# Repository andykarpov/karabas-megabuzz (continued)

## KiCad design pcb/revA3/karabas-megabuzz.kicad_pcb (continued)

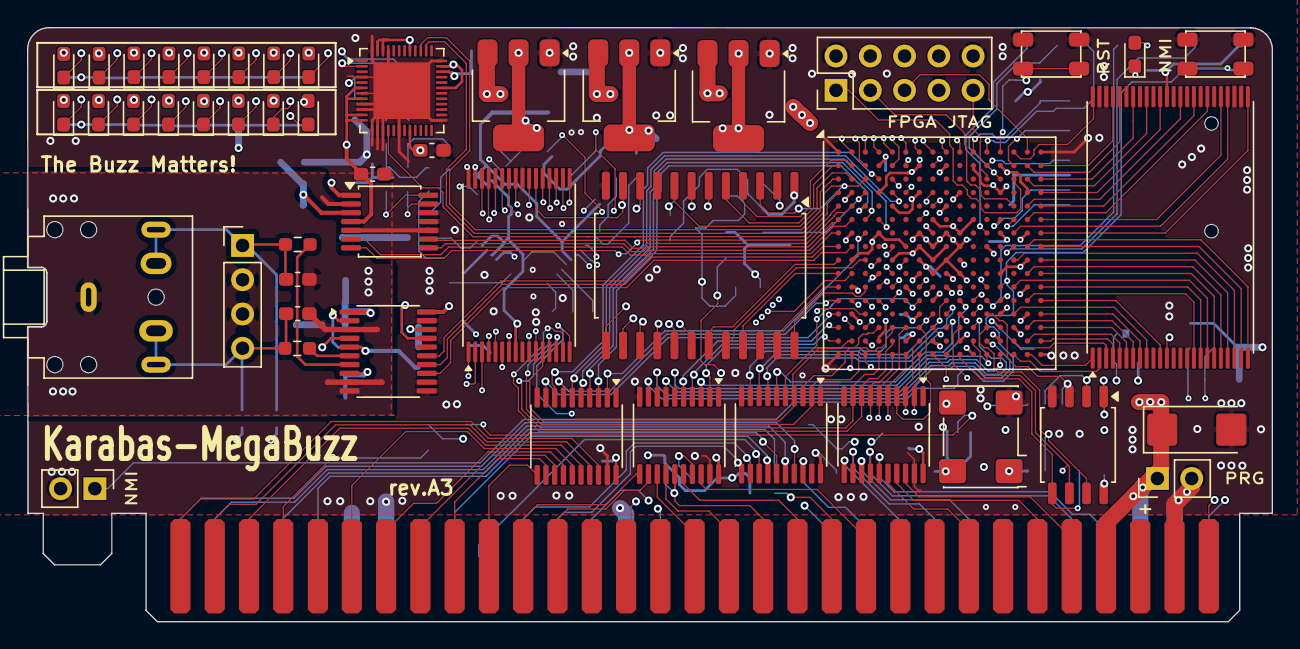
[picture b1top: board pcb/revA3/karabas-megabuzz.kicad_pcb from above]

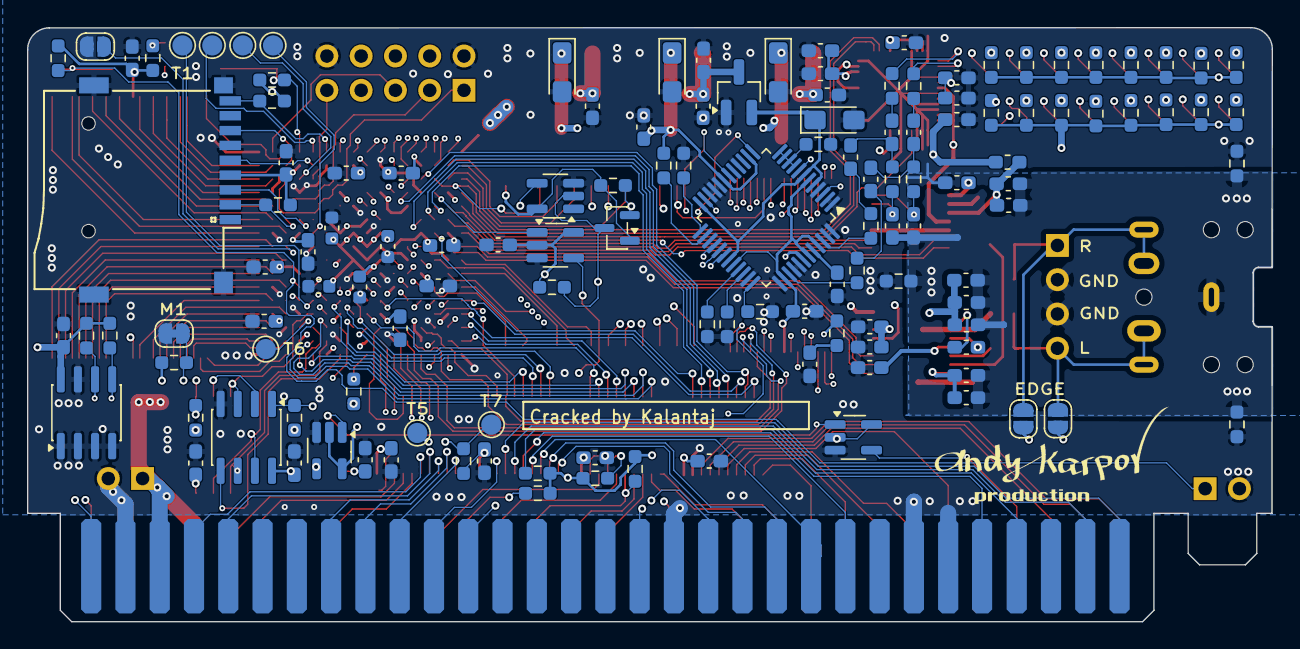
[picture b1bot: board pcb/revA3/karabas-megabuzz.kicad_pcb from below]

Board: 4 copper layers, 92.2 x 44.0 mm, 180 parts (132 on the bottom side), 245 nets.

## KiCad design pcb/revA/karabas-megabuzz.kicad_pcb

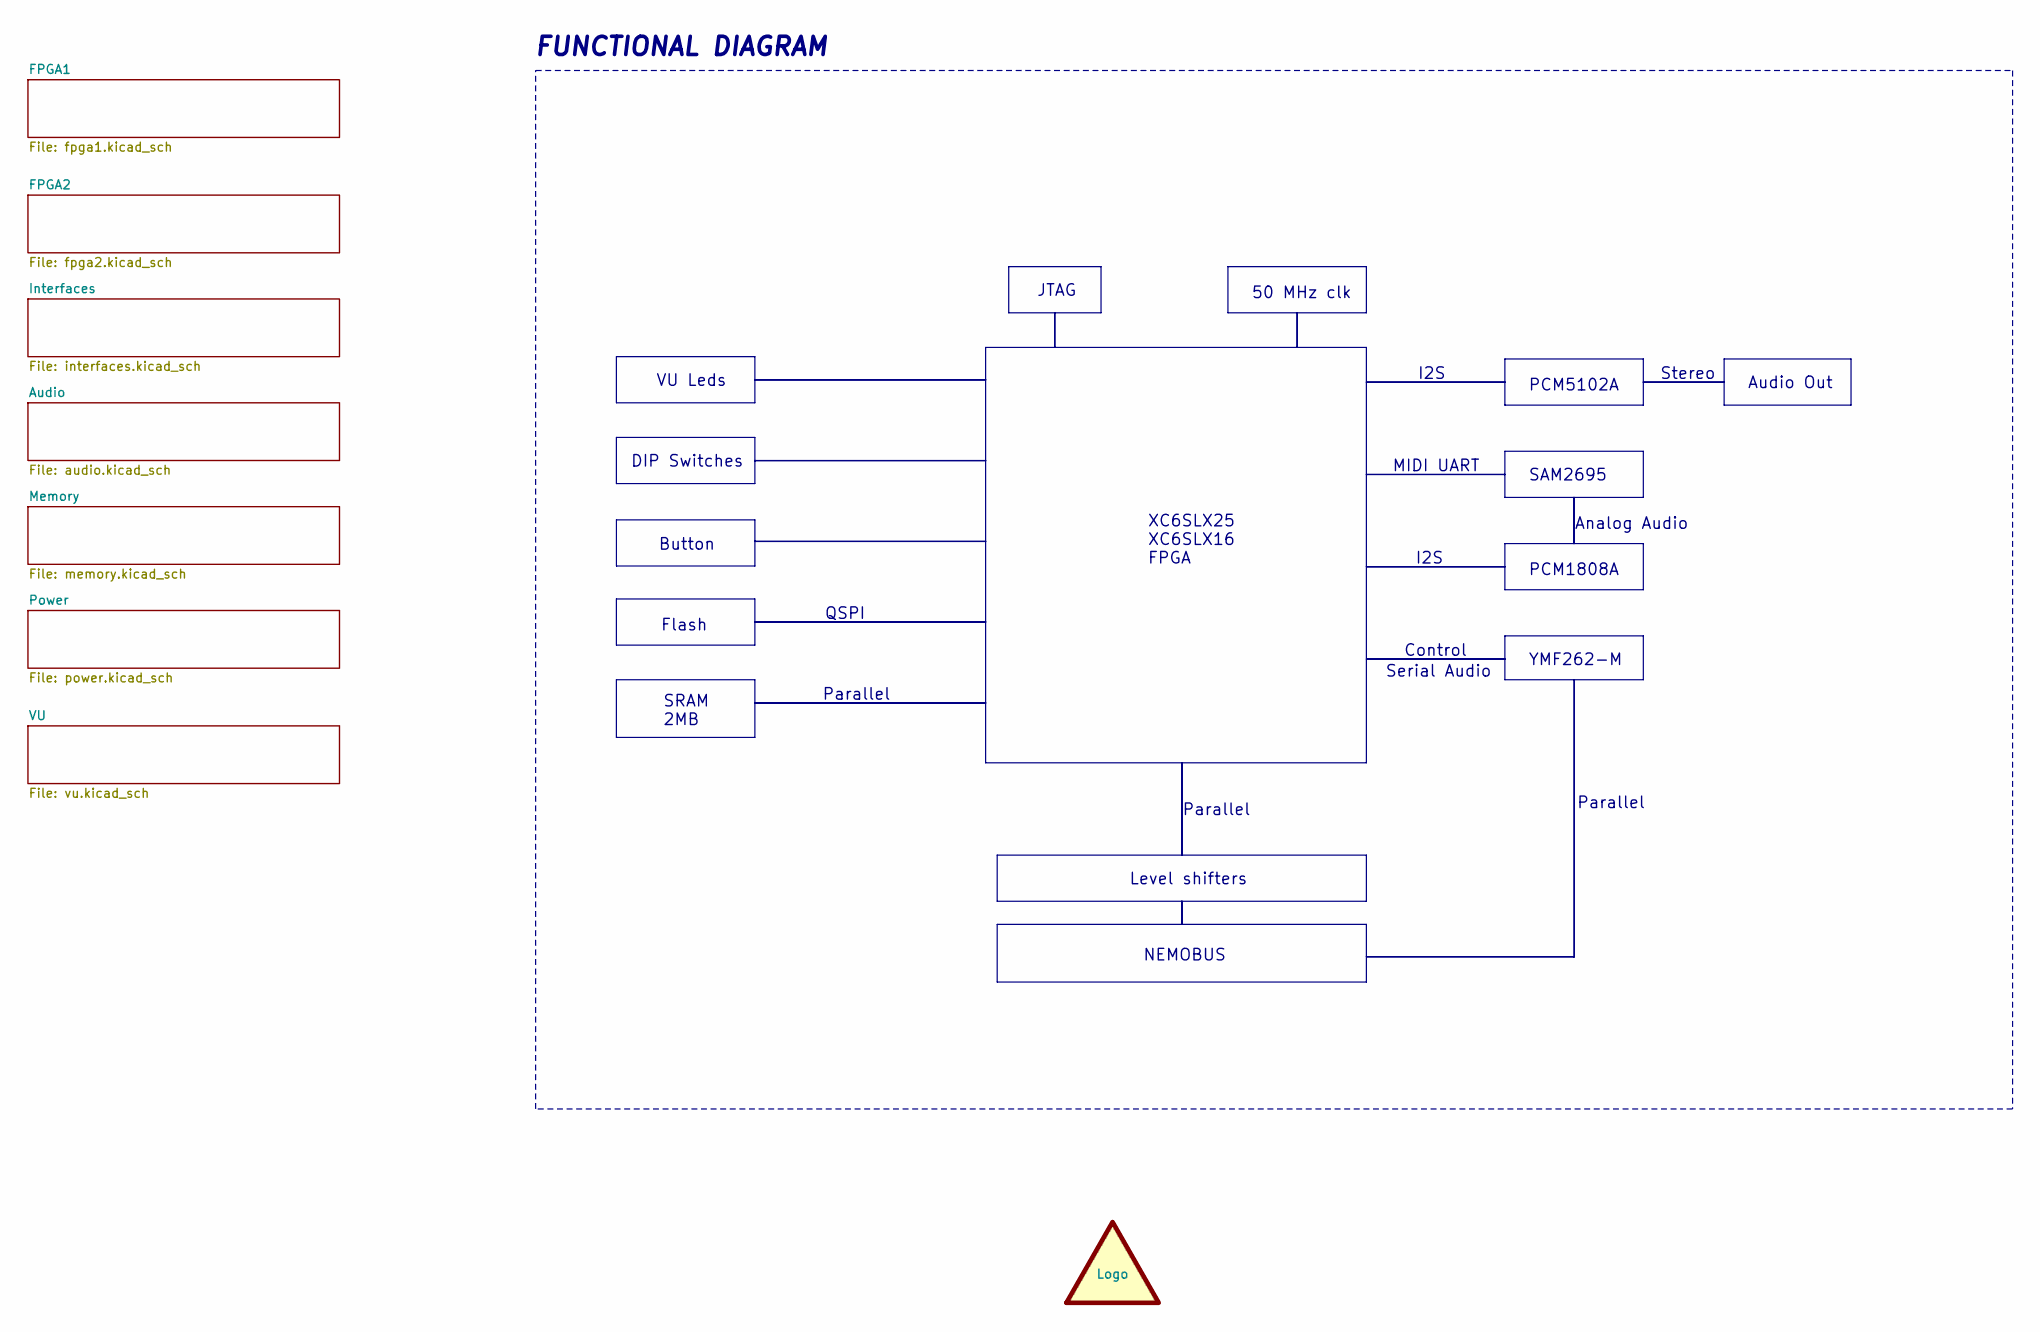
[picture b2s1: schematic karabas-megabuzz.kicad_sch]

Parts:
LOGO2: graphic; andy_karpov_logo4_silk

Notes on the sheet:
PCM5102A
VU Leds
XC6SLX25 XC6SLX16 FPGA
MIDI UART
Button
PCM1808A
Parallel
YMF262-M
NEMOBUS
DIP Switches
Audio Out
I2S
JTAG
Analog Audio
QSPI
50 MHz clk
Flash
SRAM 2MB
Level shifters
Control
Serial Audio
FUNCTIONAL DIAGRAM
SAM2695
Stereo

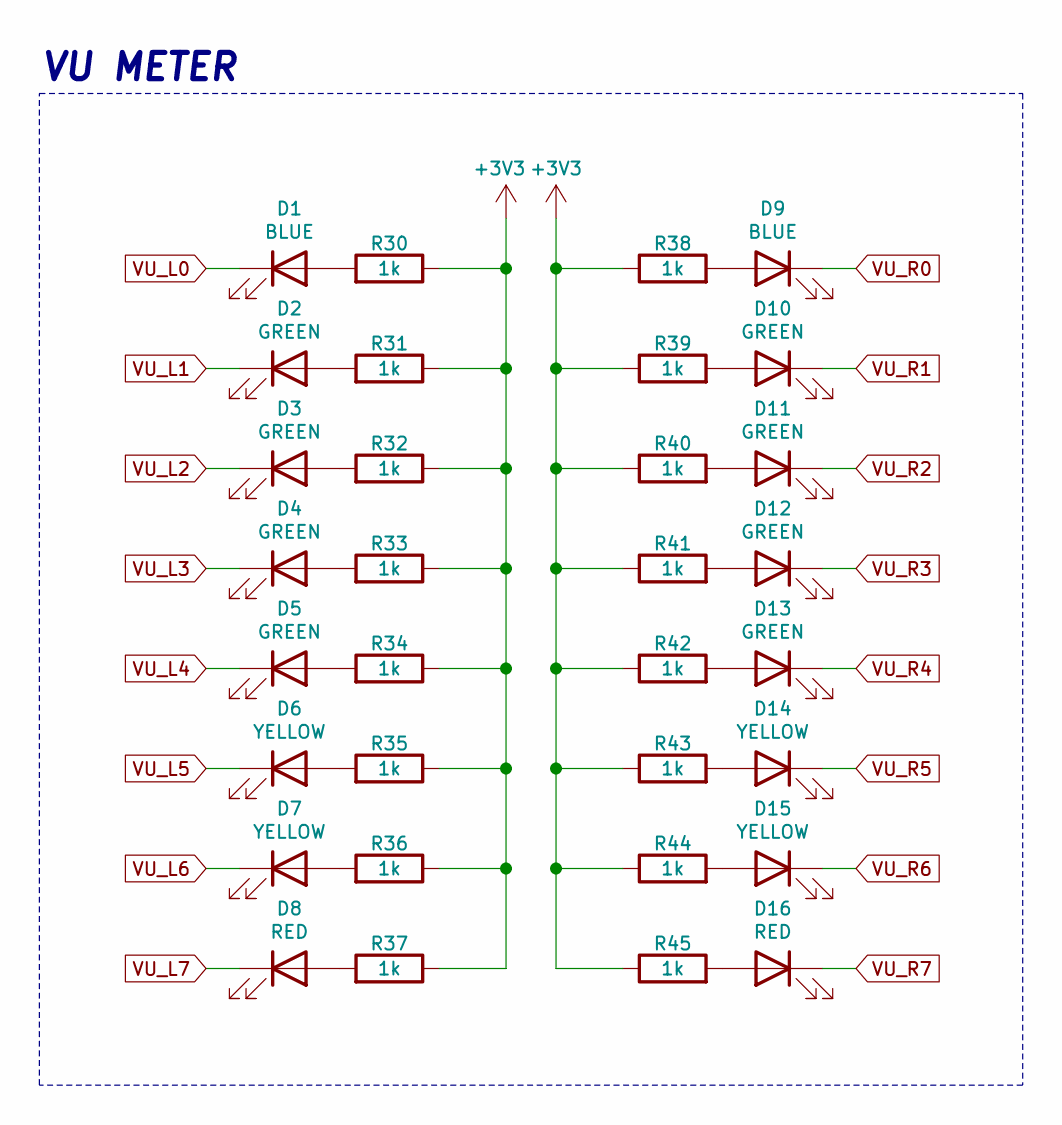
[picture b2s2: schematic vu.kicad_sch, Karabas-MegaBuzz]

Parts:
D1, D9: BLUE; LED_0603_1608Metric_Pad1.05x0.95mm_HandSolder
D2, D3, D4, D5, D10, D11, D12, D13: GREEN; LED_0603_1608Metric_Pad1.05x0.95mm_HandSolder
D6, D7, D14, D15: YELLOW; LED_0603_1608Metric_Pad1.05x0.95mm_HandSolder
D8, D16: RED; LED_0603_1608Metric_Pad1.05x0.95mm_HandSolder
R30, R31, R32, R33, R34, R35, R36, R37, R38, R39, R40, R41, R42, R43, R44, R45: 1k; R_0603_1608Metric_Pad0.98x0.95mm_HandSolder

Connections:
+3V3: R30.1, R31.1, R32.1, R33.1, R34.1, R35.1, R36.1, R37.1, R38.1, R39.1, R40.1, R41.1, R42.1, R43.1, R44.1, R45.1; also elsewhere on the board
unnamed: D1.2 (A), R30.2
unnamed: D2.2 (A), R31.2
unnamed: D3.2 (A), R32.2
unnamed: D4.2 (A), R33.2
unnamed: D5.2 (A), R34.2
unnamed: D6.2 (A), R35.2
unnamed: D7.2 (A), R36.2
unnamed: D8.2 (A), R37.2
unnamed: D9.2 (A), R38.2
unnamed: D10.2 (A), R39.2
unnamed: D11.2 (A), R40.2
unnamed: D12.2 (A), R41.2
unnamed: D13.2 (A), R42.2
unnamed: D14.2 (A), R43.2
unnamed: D15.2 (A), R44.2
unnamed: D16.2 (A), R45.2
VU_L0: D1.1 (K); also elsewhere on the board
VU_L1: D2.1 (K); also elsewhere on the board
VU_L2: D3.1 (K); also elsewhere on the board
VU_L3: D4.1 (K); also elsewhere on the board
VU_L4: D5.1 (K); also elsewhere on the board
VU_L5: D6.1 (K); also elsewhere on the board
VU_L6: D7.1 (K); also elsewhere on the board
VU_L7: D8.1 (K); also elsewhere on the board
VU_R0: D9.1 (K); also elsewhere on the board
VU_R1: D10.1 (K); also elsewhere on the board
VU_R2: D11.1 (K); also elsewhere on the board
VU_R3: D12.1 (K); also elsewhere on the board
VU_R4: D13.1 (K); also elsewhere on the board
VU_R5: D14.1 (K); also elsewhere on the board
VU_R6: D15.1 (K); also elsewhere on the board
VU_R7: D16.1 (K); also elsewhere on the board

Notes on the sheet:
VU METER

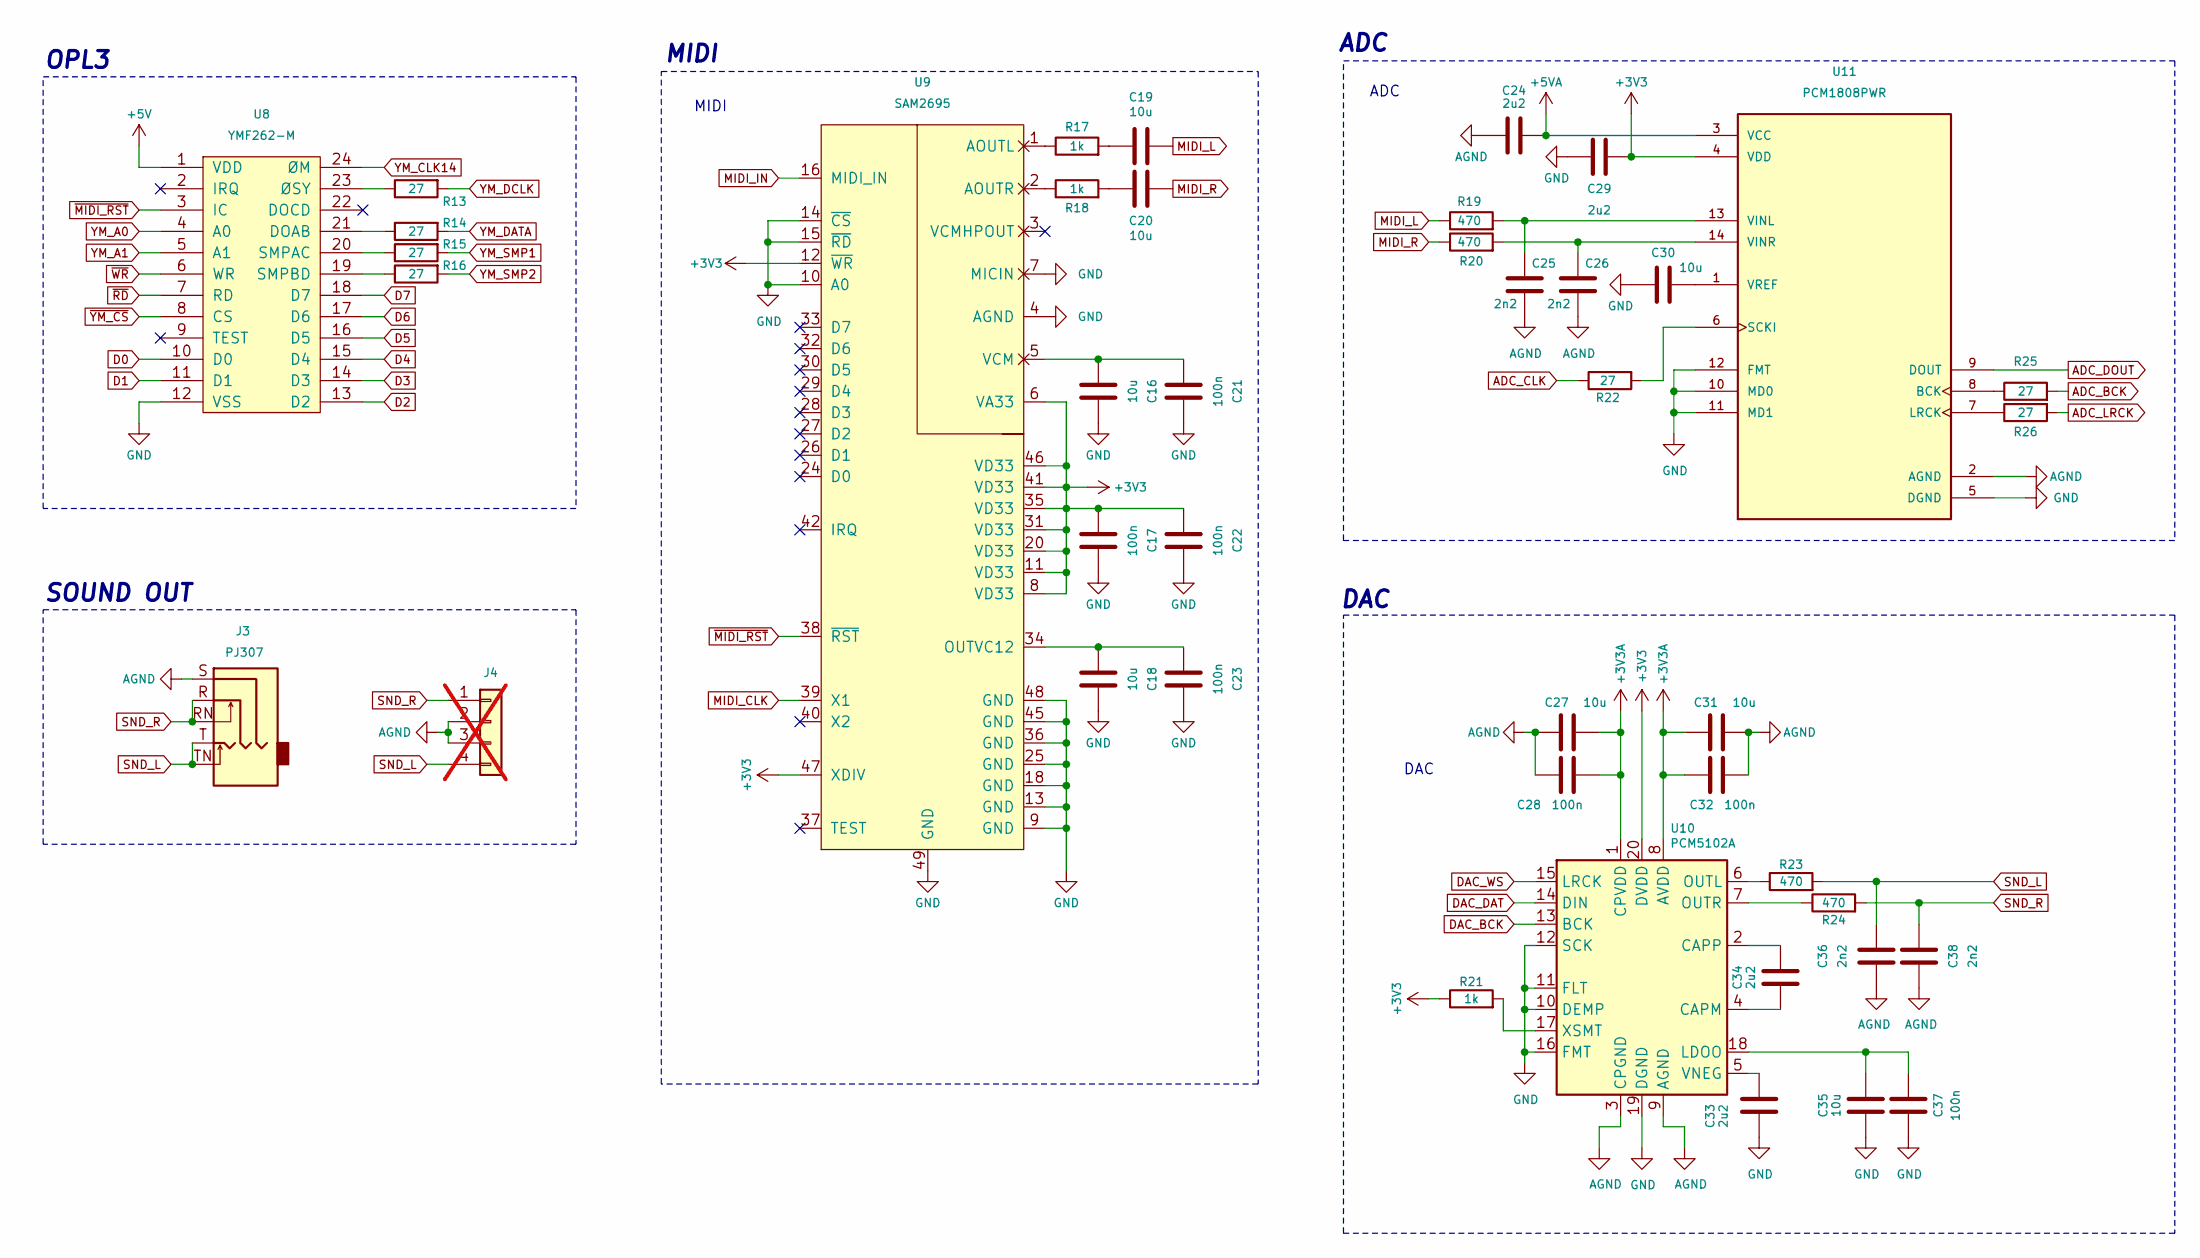
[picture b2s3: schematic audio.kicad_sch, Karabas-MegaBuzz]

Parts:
C16, C18, C19, C20, C27, C30, C31, C35: 10u; C_0603_1608Metric_Pad1.08x0.95mm_HandSolder
C17, C21, C22, C23, C28, C32, C37: 100n; C_0603_1608Metric_Pad1.08x0.95mm_HandSolder
C24, C29, C33, C34: 2u2; C_0603_1608Metric_Pad1.08x0.95mm_HandSolder
C25, C26, C36, C38: 2n2; C_0603_1608Metric_Pad1.08x0.95mm_HandSolder
J3: PJ307; Jack_3.5mm_CUI_SJ1-3525N_Horizontal
J4: Conn_01x04; PinHeader_1x04_P2.54mm_Vertical; not fitted
R13, R14, R15, R16, R22, R25, R26: 27; R_0603_1608Metric_Pad0.98x0.95mm_HandSolder
R17, R18, R21: 1k; R_0603_1608Metric_Pad0.98x0.95mm_HandSolder
R19, R20, R23, R24: 470; R_0603_1608Metric_Pad0.98x0.95mm_HandSolder
U8: YMF262-M; ymf-262-m
U9: SAM2695; QFN-48-1EP_6x6mm_P0.4mm_EP4.2x4.2mm
U10: PCM5102A; TSSOP-20_4.4x6.5mm_P0.65mm
U11: PCM1808PWR; TSSOP-14_4.4x5mm_P0.65mm; PARTREV B

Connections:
+3V3: C17.1, C22.1, C29.1, R21.1, U9.6 (VA33), U9.8 (VD33), U9.11 (VD33), U9.12 (~WR), U9.20 (VD33), U9.31 (VD33), U9.35 (VD33), U9.41 (VD33), U9.46 (VD33), U9.47 (XDIV), U10.20 (DVDD), U11.4 (VDD); also elsewhere on the board
+3V3A: C27.1, C28.1, C31.2, C32.2, U10.1 (CPVDD), U10.8 (AVDD); also elsewhere on the board
+5V: U8.1 (VDD); also elsewhere on the board
+5VA: C24.2, U11.3 (VCC); also elsewhere on the board
ADC_BCK: R25.2; also elsewhere on the board
ADC_CLK: R22.1; also elsewhere on the board
ADC_DOUT: U11.9 (DOUT); also elsewhere on the board
ADC_LRCK: R26.2; also elsewhere on the board
AGND: C24.1, C25.2, C26.2, C27.2, C28.2, C31.1, C32.1, C36.1, C38.1, J3.S, J4.2, J4.3, U10.3 (CPGND), U10.9 (AGND), U11.2 (AGND); also elsewhere on the board
D0: U8.10 (D0); also elsewhere on the board
D1: U8.11 (D1); also elsewhere on the board
D2: U8.13 (D2); also elsewhere on the board
D3: U8.14 (D3); also elsewhere on the board
D4: U8.15 (D4); also elsewhere on the board
D5: U8.16 (D5); also elsewhere on the board
D6: U8.17 (D6); also elsewhere on the board
D7: U8.18 (D7); also elsewhere on the board
DAC_BCK: U10.13 (BCK); also elsewhere on the board
DAC_DAT: U10.14 (DIN); also elsewhere on the board
DAC_WS: U10.15 (LRCK); also elsewhere on the board
GND: C16.2, C17.2, C18.2, C21.2, C22.2, C23.2, C29.2, C30.1, C33.1, C35.1, C37.1, U8.12 (VSS), U9.4 (AGND), U9.7 (MICIN), U9.9 (GND), U9.10 (A0), U9.13 (GND), U9.14 (~CS), U9.15 (~RD), U9.18 (GND), U9.25 (GND), U9.36 (GND), U9.45 (GND), U9.48 (GND), U9.49 (GND), U10.10 (DEMP), U10.11 (FLT), U10.12 (SCK), U10.16 (FMT), U10.19 (DGND), U11.5 (DGND), U11.10 (MD0), U11.11 (MD1), U11.12 (FMT); also elsewhere on the board
MIDI_CLK: U9.39 (X1); also elsewhere on the board
MIDI_IN: U9.16 (MIDI_IN); also elsewhere on the board
MIDI_L: C19.2, R19.1
MIDI_R: C20.2, R20.1
unnamed: C19.1, R17.2
unnamed: C20.1, R18.2
unnamed: R14.1, U8.21 (DOAB)
unnamed: R15.1, U8.20 (SMPAC)
unnamed: R16.1, U8.19 (SMPBD)
unnamed: R13.1, U8.23 (ØSY)
unnamed: R17.1, U9.1 (AOUTL)
unnamed: R18.1, U9.2 (AOUTR)
unnamed: C18.1, C23.1, U9.34 (OUTVC12)
unnamed: C16.1, C21.1, U9.5 (VCM)
unnamed: C34.1, U10.4 (CAPM)
unnamed: C34.2, U10.2 (CAPP)
unnamed: C35.2, C37.2, U10.18 (LDOO)
unnamed: R23.1, U10.6 (OUTL)
unnamed: R24.1, U10.7 (OUTR)
unnamed: C33.2, U10.5 (VNEG)
unnamed: R21.2, U10.17 (XSMT)
unnamed: R25.1, U11.8 (BCK)
unnamed: R26.1, U11.7 (LRCK)
unnamed: R22.2, U11.6 (SCKI)
unnamed: C25.1, R19.2, U11.13 (VINL)
unnamed: C26.1, R20.2, U11.14 (VINR)
unnamed: C30.2, U11.1 (VREF)
SND_L: C36.2, J3.T, J3.TN, J4.4, R23.2
SND_R: C38.2, J3.R, J3.RN, J4.1, R24.2
YM_A0: U8.4 (A0); also elsewhere on the board
YM_A1: U8.5 (A1); also elsewhere on the board
YM_CLK14: U8.24 (ØM); also elsewhere on the board
YM_DATA: R14.2; also elsewhere on the board
YM_DCLK: R13.2; also elsewhere on the board
YM_SMP1: R15.2; also elsewhere on the board
YM_SMP2: R16.2; also elsewhere on the board
~MIDI_RST: U8.3 (IC), U9.38 (~RST); also elsewhere on the board
~RD: U8.7 (RD); also elsewhere on the board
~WR: U8.6 (WR); also elsewhere on the board
~YM_CS: U8.8 (CS); also elsewhere on the board

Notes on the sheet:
SOUND OUT
ADC
MIDI
DAC
OPL3

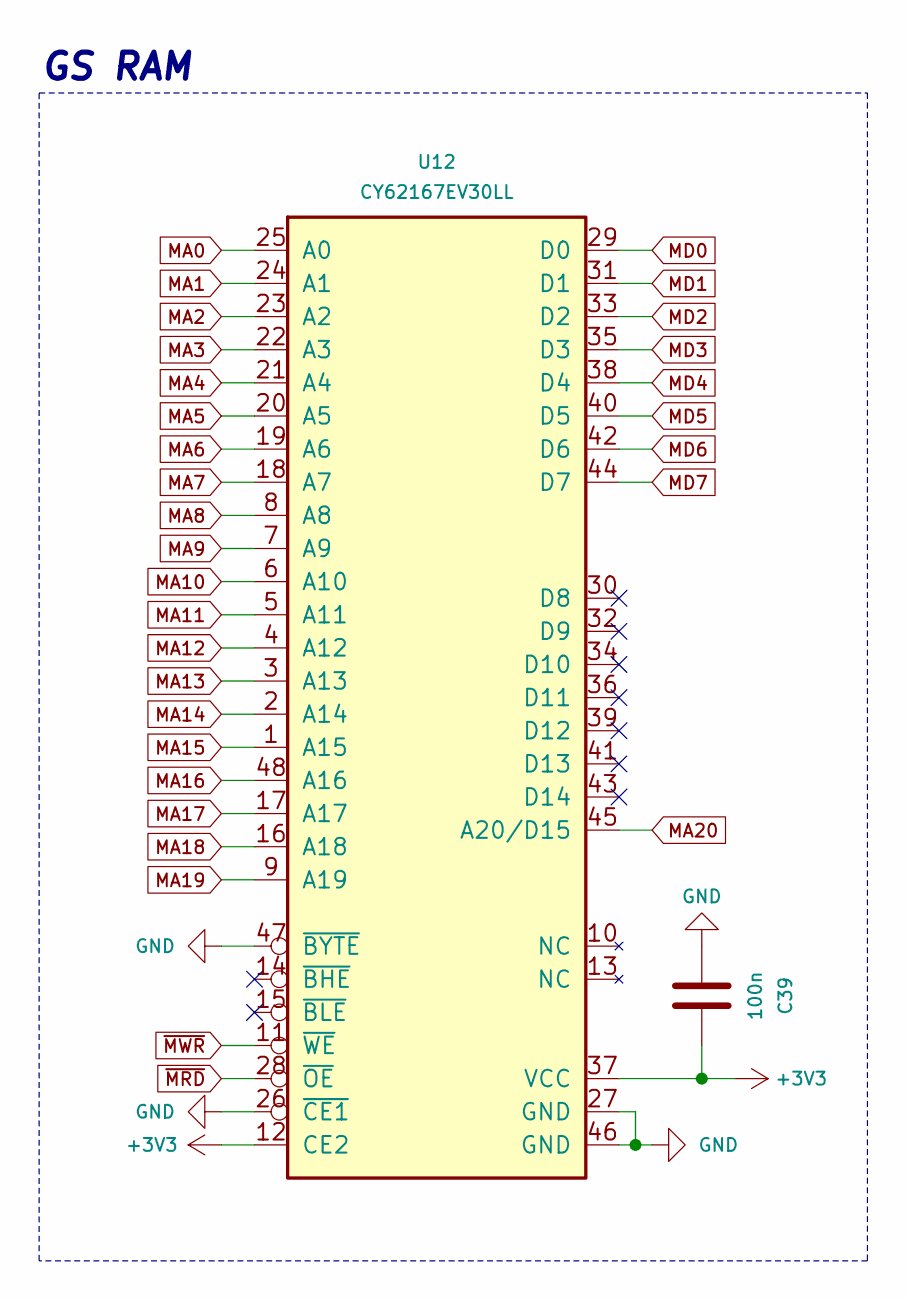
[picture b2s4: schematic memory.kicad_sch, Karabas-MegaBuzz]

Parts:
C39: 100n; C_0603_1608Metric_Pad1.08x0.95mm_HandSolder
U12: CY62167EV30LL; TSOP-I-48_18.4x12mm_P0.5mm

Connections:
+3V3: C39.2, U12.12 (CE2), U12.37 (VCC); also elsewhere on the board
GND: C39.1, U12.26 (~CE1), U12.27 (GND), U12.46 (GND), U12.47 (~BYTE); also elsewhere on the board
MA0: U12.25 (A0); also elsewhere on the board
MA1: U12.24 (A1); also elsewhere on the board
MA2: U12.23 (A2); also elsewhere on the board
MA3: U12.22 (A3); also elsewhere on the board
MA4: U12.21 (A4); also elsewhere on the board
MA5: U12.20 (A5); also elsewhere on the board
MA6: U12.19 (A6); also elsewhere on the board
MA7: U12.18 (A7); also elsewhere on the board
MA8: U12.8 (A8); also elsewhere on the board
MA9: U12.7 (A9); also elsewhere on the board
MA10: U12.6 (A10); also elsewhere on the board
MA11: U12.5 (A11); also elsewhere on the board
MA12: U12.4 (A12); also elsewhere on the board
MA13: U12.3 (A13); also elsewhere on the board
MA14: U12.2 (A14); also elsewhere on the board
MA15: U12.1 (A15); also elsewhere on the board
MA16: U12.48 (A16); also elsewhere on the board
MA17: U12.17 (A17); also elsewhere on the board
MA18: U12.16 (A18); also elsewhere on the board
MA19: U12.9 (A19); also elsewhere on the board
MA20: U12.45 (A20/D15); also elsewhere on the board
MD0: U12.29 (D0); also elsewhere on the board
MD1: U12.31 (D1); also elsewhere on the board
MD2: U12.33 (D2); also elsewhere on the board
MD3: U12.35 (D3); also elsewhere on the board
MD4: U12.38 (D4); also elsewhere on the board
MD5: U12.40 (D5); also elsewhere on the board
MD6: U12.42 (D6); also elsewhere on the board
MD7: U12.44 (D7); also elsewhere on the board
~MRD: U12.28 (~OE); also elsewhere on the board
~MWR: U12.11 (~WE); also elsewhere on the board

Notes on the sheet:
GS RAM

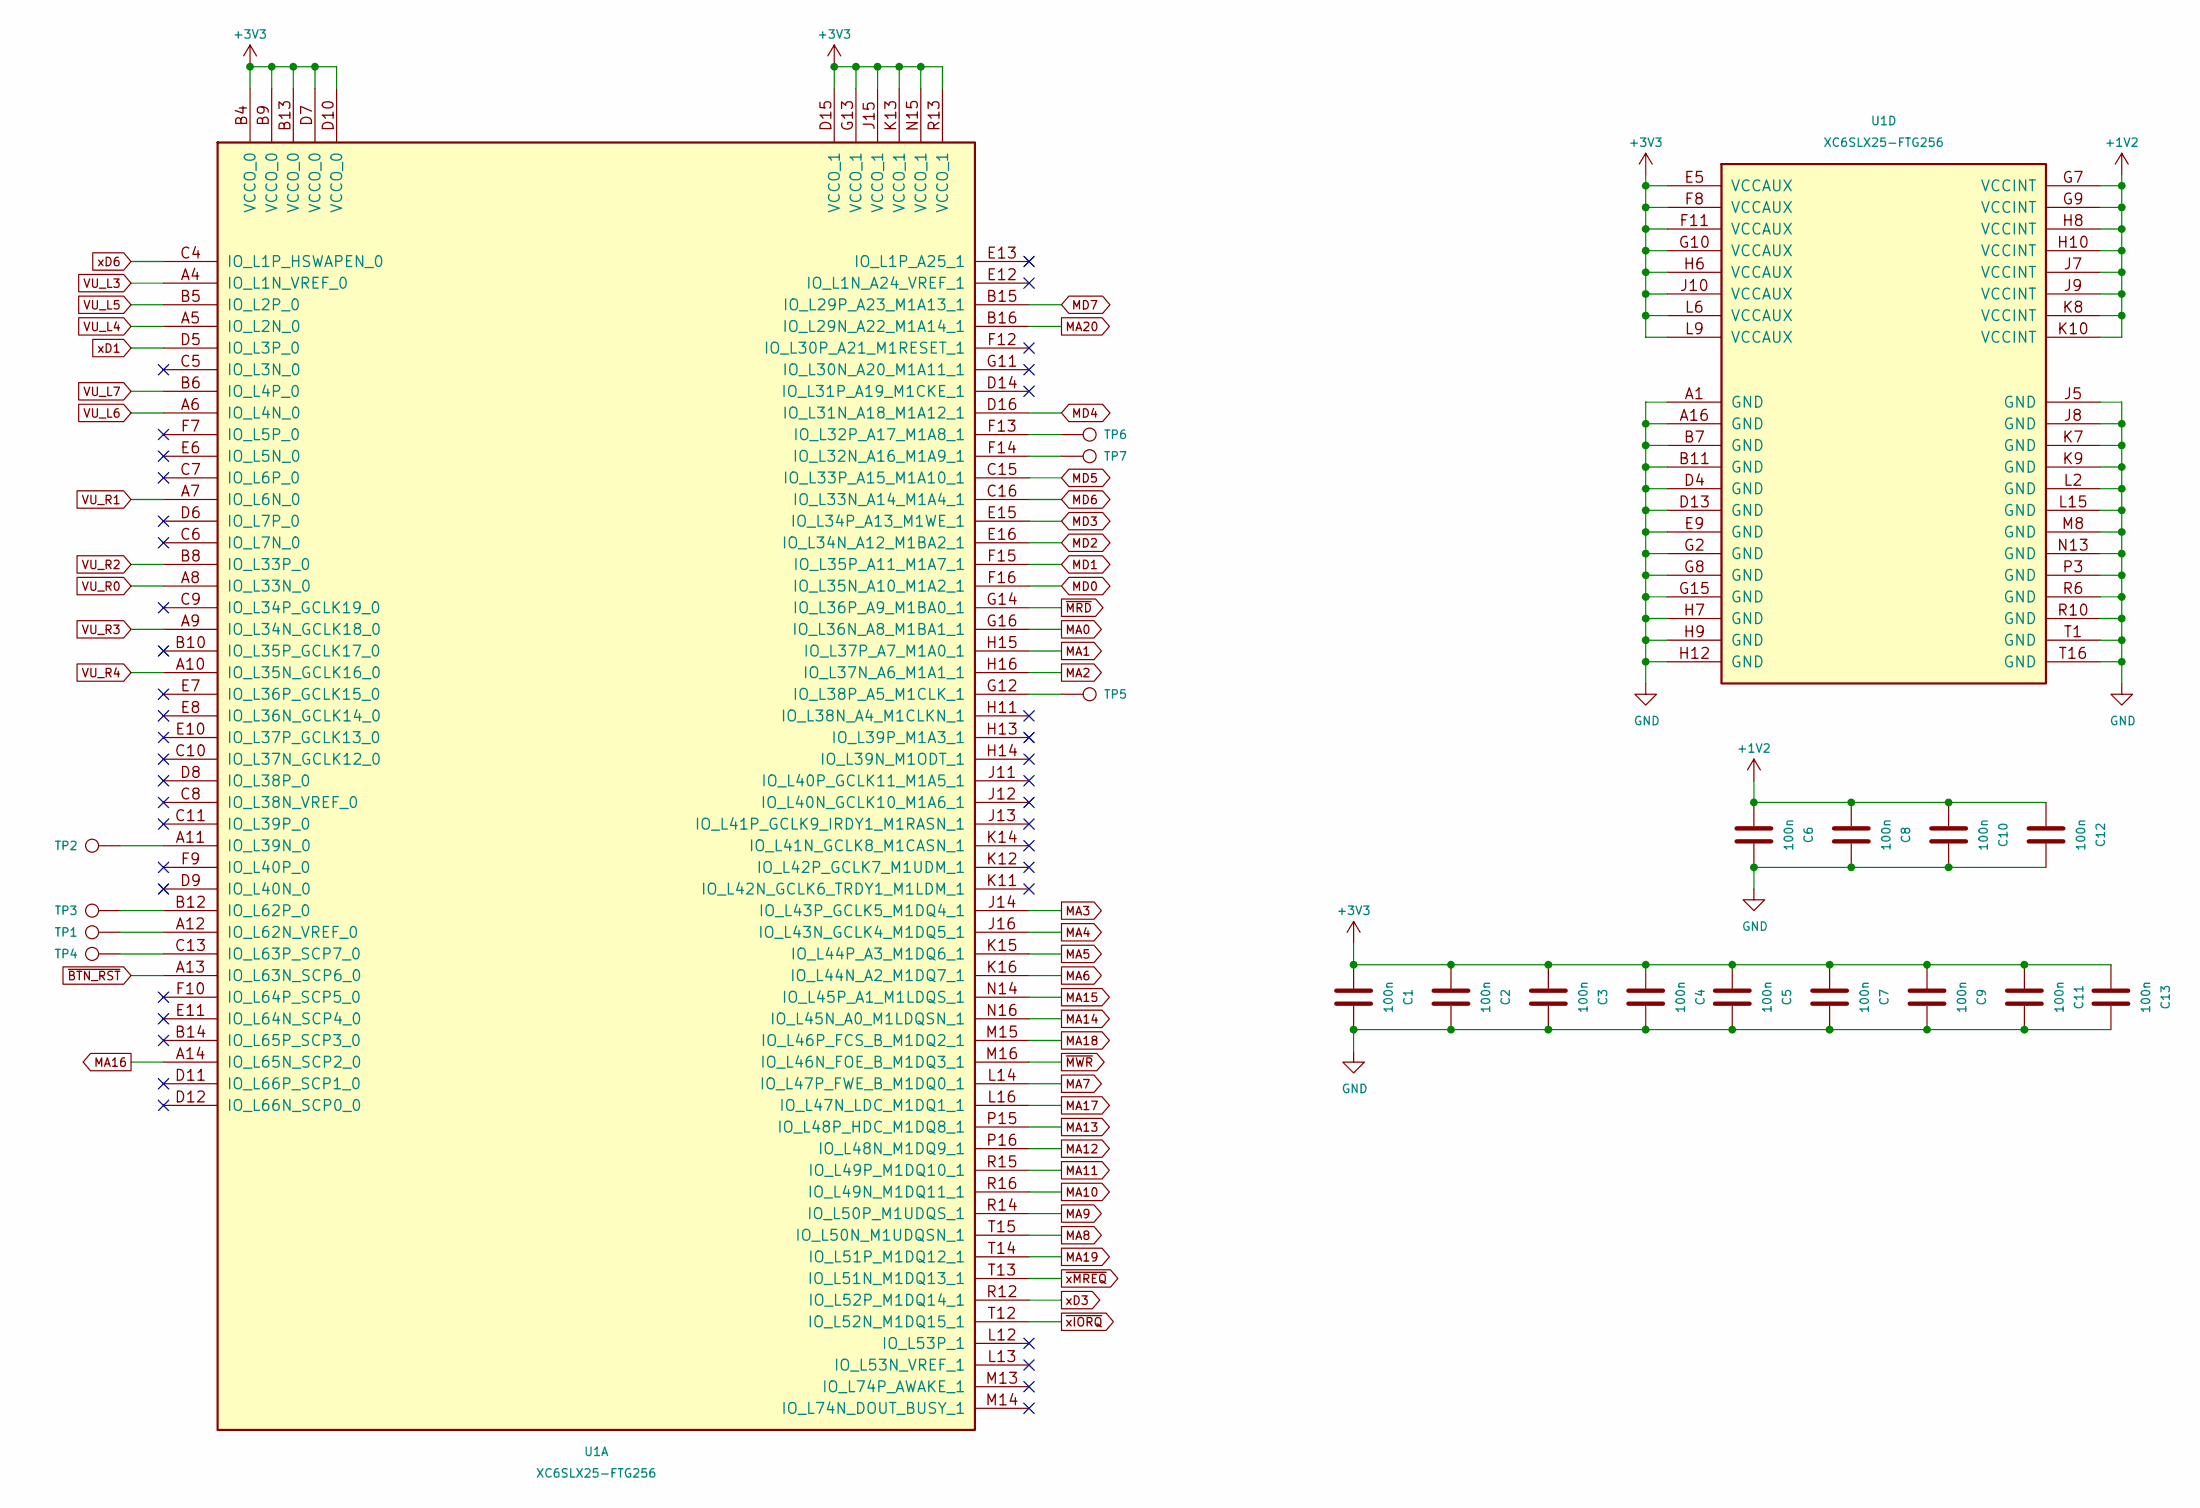
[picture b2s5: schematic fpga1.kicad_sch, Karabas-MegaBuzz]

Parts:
C1, C2, C3, C4, C5, C7, C9, C11, C13: 100n; C_0603_1608Metric_Pad1.08x0.95mm_HandSolder
C6, C8, C10, C12: 100n; C_0603_1608Metric
TP1, TP2, TP3, TP4, TP5, TP6, TP7: TestPoint; TestPoint_Pad_D1.5mm
U1: XC6SLX25-FTG256; BGA-256_17.0x17.0mm_Layout16x16_P1.0mm_Ball0.5mm_Pad0.4mm_N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

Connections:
+1V2: C6.1, C8.1, C10.1, C12.1, U1.G7 (VCCINT), U1.G9 (VCCINT), U1.H8 (VCCINT), U1.H10 (VCCINT), U1.J7 (VCCINT), U1.J9 (VCCINT), U1.K8 (VCCINT), U1.K10 (VCCINT); also elsewhere on the board
+3V3: C1.1, C2.1, C3.1, C4.1, C5.1, C7.1, C9.1, C11.1, C13.1, U1.B4 (VCCO_0), U1.B9 (VCCO_0), U1.B13 (VCCO_0), U1.D7 (VCCO_0), U1.D10 (VCCO_0), U1.D15 (VCCO_1), U1.E5 (VCCAUX), U1.F8 (VCCAUX), U1.F11 (VCCAUX), U1.G10 (VCCAUX), U1.G13 (VCCO_1), U1.H6 (VCCAUX), U1.J10 (VCCAUX), U1.J15 (VCCO_1), U1.K13 (VCCO_1), U1.L6 (VCCAUX), U1.L9 (VCCAUX), U1.N15 (VCCO_1), U1.R13 (VCCO_1); also elsewhere on the board
GND: C1.2, C2.2, C3.2, C4.2, C5.2, C6.2, C7.2, C8.2, C9.2, C10.2, C11.2, C12.2, C13.2, U1.A1 (GND), U1.A16 (GND), U1.B7 (GND), U1.B11 (GND), U1.D4 (GND), U1.D13 (GND), U1.E9 (GND), U1.G2 (GND), U1.G8 (GND), U1.G15 (GND), U1.H7 (GND), U1.H9 (GND), U1.H12 (GND), U1.J5 (GND), U1.J8 (GND), U1.K7 (GND), U1.K9 (GND), U1.L2 (GND), U1.L15 (GND), U1.M8 (GND), U1.N13 (GND), U1.P3 (GND), U1.R6 (GND), U1.R10 (GND), U1.T1 (GND), U1.T16 (GND); also elsewhere on the board
MA0: U1.G16 (IO_L36N_A8_M1BA1_1); also elsewhere on the board
MA1: U1.H15 (IO_L37P_A7_M1A0_1); also elsewhere on the board
MA2: U1.H16 (IO_L37N_A6_M1A1_1); also elsewhere on the board
MA3: U1.J14 (IO_L43P_GCLK5_M1DQ4_1); also elsewhere on the board
MA4: U1.J16 (IO_L43N_GCLK4_M1DQ5_1); also elsewhere on the board
MA5: U1.K15 (IO_L44P_A3_M1DQ6_1); also elsewhere on the board
MA6: U1.K16 (IO_L44N_A2_M1DQ7_1); also elsewhere on the board
MA7: U1.L14 (IO_L47P_FWE_B_M1DQ0_1); also elsewhere on the board
MA8: U1.T15 (IO_L50N_M1UDQSN_1); also elsewhere on the board
MA9: U1.R14 (IO_L50P_M1UDQS_1); also elsewhere on the board
MA10: U1.R16 (IO_L49N_M1DQ11_1); also elsewhere on the board
MA11: U1.R15 (IO_L49P_M1DQ10_1); also elsewhere on the board
MA12: U1.P16 (IO_L48N_M1DQ9_1); also elsewhere on the board
MA13: U1.P15 (IO_L48P_HDC_M1DQ8_1); also elsewhere on the board
MA14: U1.N16 (IO_L45N_A0_M1LDQSN_1); also elsewhere on the board
MA15: U1.N14 (IO_L45P_A1_M1LDQS_1); also elsewhere on the board
MA16: U1.A14 (IO_L65N_SCP2_0); also elsewhere on the board
MA17: U1.L16 (IO_L47N_LDC_M1DQ1_1); also elsewhere on the board
MA18: U1.M15 (IO_L46P_FCS_B_M1DQ2_1); also elsewhere on the board
MA19: U1.T14 (IO_L51P_M1DQ12_1); also elsewhere on the board
MA20: U1.B16 (IO_L29N_A22_M1A14_1); also elsewhere on the board
MD0: U1.F16 (IO_L35N_A10_M1A2_1); also elsewhere on the board
MD1: U1.F15 (IO_L35P_A11_M1A7_1); also elsewhere on the board
MD2: U1.E16 (IO_L34N_A12_M1BA2_1); also elsewhere on the board
MD3: U1.E15 (IO_L34P_A13_M1WE_1); also elsewhere on the board
MD4: U1.D16 (IO_L31N_A18_M1A12_1); also elsewhere on the board
MD5: U1.C15 (IO_L33P_A15_M1A10_1); also elsewhere on the board
MD6: U1.C16 (IO_L33N_A14_M1A4_1); also elsewhere on the board
MD7: U1.B15 (IO_L29P_A23_M1A13_1); also elsewhere on the board
unnamed: TP7.1 (1_1), U1.F14 (IO_L32N_A16_M1A9_1)
unnamed: TP6.1 (1_1), U1.F13 (IO_L32P_A17_M1A8_1)
unnamed: TP5.1 (1_1), U1.G12 (IO_L38P_A5_M1CLK_1)
unnamed: TP2.1 (1_1), U1.A11 (IO_L39N_0)
unnamed: TP1.1 (1_1), U1.A12 (IO_L62N_VREF_0)
unnamed: TP3.1 (1_1), U1.B12 (IO_L62P_0)
unnamed: TP4.1 (1_1), U1.C13 (IO_L63P_SCP7_0)
VU_L3: U1.A4 (IO_L1N_VREF_0); also elsewhere on the board
VU_L4: U1.A5 (IO_L2N_0); also elsewhere on the board
VU_L5: U1.B5 (IO_L2P_0); also elsewhere on the board
VU_L6: U1.A6 (IO_L4N_0); also elsewhere on the board
VU_L7: U1.B6 (IO_L4P_0); also elsewhere on the board
VU_R0: U1.A8 (IO_L33N_0); also elsewhere on the board
VU_R1: U1.A7 (IO_L6N_0); also elsewhere on the board
VU_R2: U1.B8 (IO_L33P_0); also elsewhere on the board
VU_R3: U1.A9 (IO_L34N_GCLK18_0); also elsewhere on the board
VU_R4: U1.A10 (IO_L35N_GCLK16_0); also elsewhere on the board
xD1: U1.D5 (IO_L3P_0); also elsewhere on the board
xD3: U1.R12 (IO_L52P_M1DQ14_1); also elsewhere on the board
xD6: U1.C4 (IO_L1P_HSWAPEN_0); also elsewhere on the board
~BTN_RST: U1.A13 (IO_L63N_SCP6_0); also elsewhere on the board
~MRD: U1.G14 (IO_L36P_A9_M1BA0_1); also elsewhere on the board
~MWR: U1.M16 (IO_L46N_FOE_B_M1DQ3_1); also elsewhere on the board
~xIORQ: U1.T12 (IO_L52N_M1DQ15_1); also elsewhere on the board
~xMREQ: U1.T13 (IO_L51N_M1DQ13_1); also elsewhere on the board

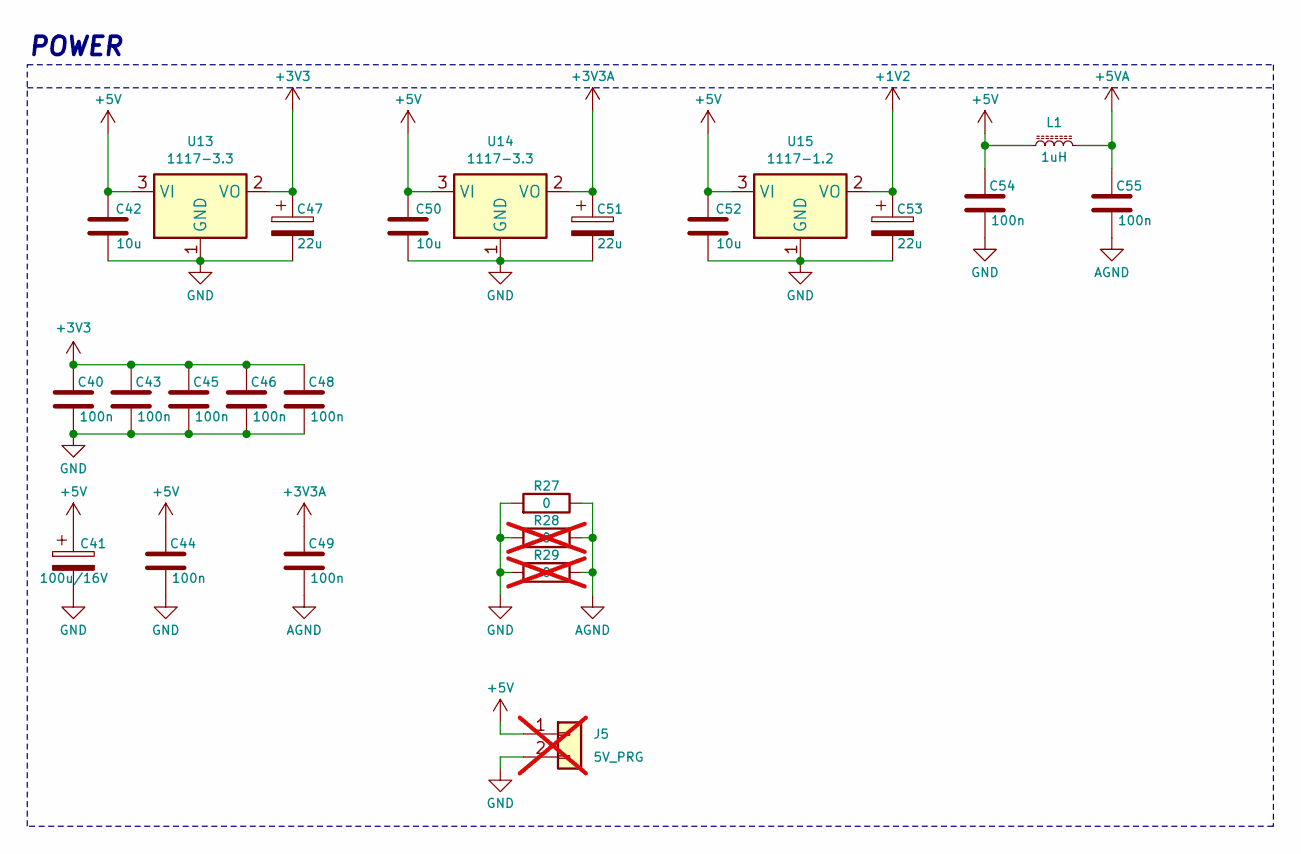
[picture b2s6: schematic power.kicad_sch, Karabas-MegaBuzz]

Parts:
C40, C43, C44, C45, C46, C48, C49, C54, C55: 100n; C_0603_1608Metric_Pad1.08x0.95mm_HandSolder
C41: 100u/16V; CP_Elec_6.3x7.7
C42, C50, C52: 10u; C_0603_1608Metric_Pad1.08x0.95mm_HandSolder
C47, C51, C53: 22u; CP_EIA-3216-18_Kemet-A_HandSolder
J5: 5V_PRG; PinHeader_1x02_P2.54mm_Vertical; not fitted
L1: 1uH; L_0603_1608Metric_Pad1.05x0.95mm_HandSolder
R27: 0; R_0603_1608Metric_Pad0.98x0.95mm_HandSolder
R28, R29: 0; R_0603_1608Metric_Pad0.98x0.95mm_HandSolder; not fitted
U13, U14: 1117-3.3; SOT-223-3_TabPin2
U15: 1117-1.2; SOT-223-3_TabPin2

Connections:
+1V2: C53.1, U15.2 (VO); also elsewhere on the board
+3V3: C40.1, C43.1, C45.1, C46.1, C47.1, C48.1, U13.2 (VO); also elsewhere on the board
+3V3A: C49.1, C51.1, U14.2 (VO); also elsewhere on the board
+5V: C41.1, C42.1, C44.2, C50.1, C52.1, C54.1, J5.1, L1.1, U13.3 (VI), U14.3 (VI), U15.3 (VI); also elsewhere on the board
+5VA: C55.1, L1.2; also elsewhere on the board
AGND: C49.2, C55.2, R27.1, R28.1, R29.1; also elsewhere on the board
GND: C40.2, C41.2, C42.2, C43.2, C44.1, C45.2, C46.2, C47.2, C48.2, C50.2, C51.2, C52.2, C53.2, C54.2, J5.2, R27.2, R28.2, R29.2, U13.1 (GND), U14.1 (GND), U15.1 (GND); also elsewhere on the board

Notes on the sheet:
POWER
